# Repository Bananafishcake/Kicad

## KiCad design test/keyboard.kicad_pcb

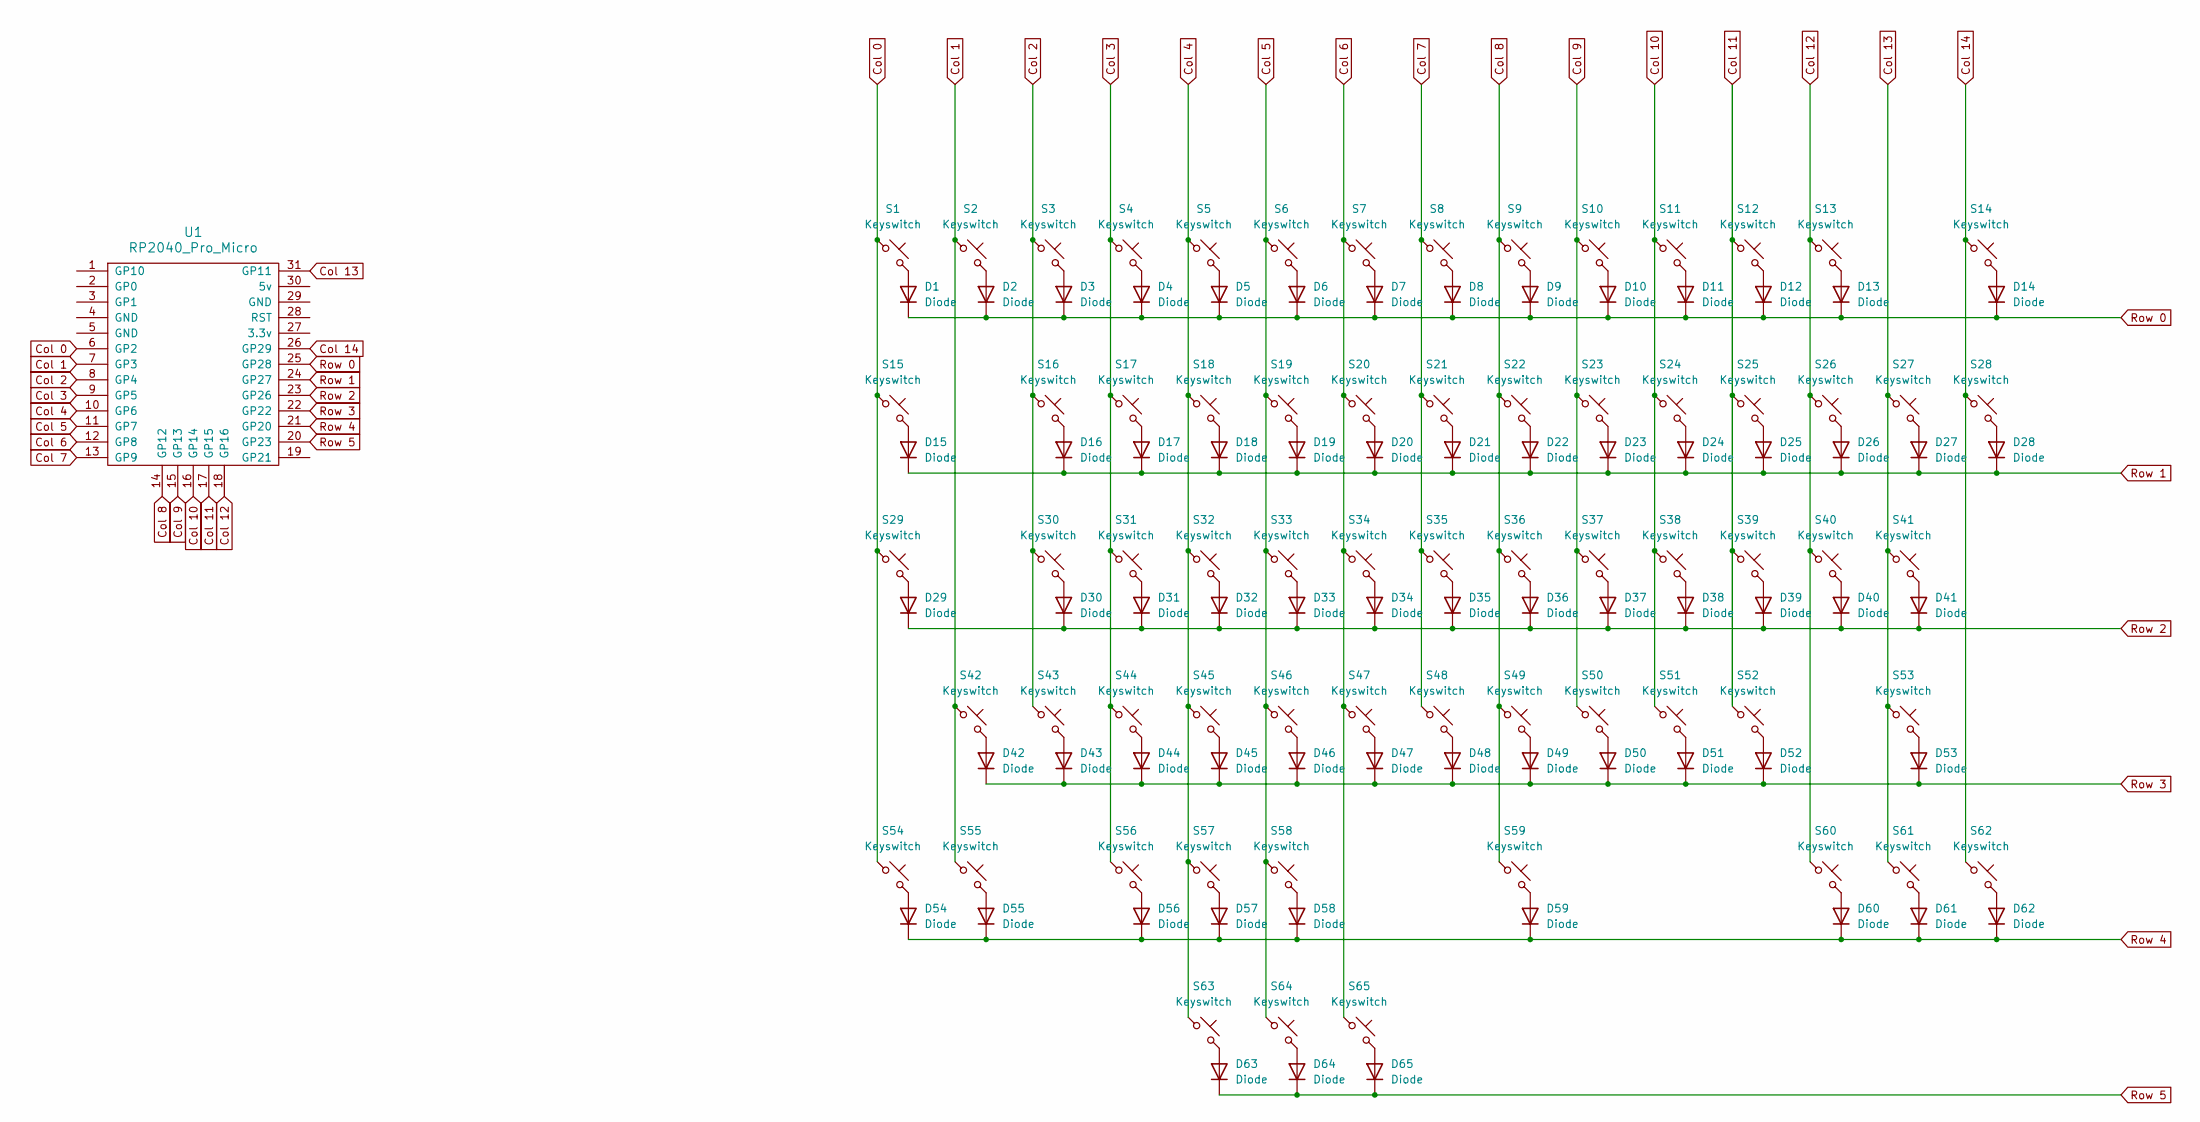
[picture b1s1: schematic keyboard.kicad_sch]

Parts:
D1, D2, D3, D4, D5, D6, D7, D8, D9, D10, D11, D12, D13, D14, D15, D16, D17, D18, D19, D20, D21, D22, D23, D24, D25, D26, D27, D28, D29, D30, D31, D32, D33, D34, D35, D36, D37, D38, D39, D40, D41, D42, D43, D44, D45, D46, D47, D48, D49, D50, D51, D52, D53, D54, D55, D56, D57, D58, D59, D60, D61, D62, D63, D64, D65: Diode; Diode_DO-35
S1, S2, S3, S4, S5, S6, S7, S8, S9, S10, S11, S12, S13, S16, S17, S18, S19, S20, S21, S22, S23, S24, S25, S26, S27, S30, S31, S32, S33, S34, S35, S36, S37, S38, S39, S40, S43, S44, S45, S46, S47, S48, S49, S50, S51, S52, S57, S58, S60, S61, S62, S63, S64, S65: Keyswitch; MX_PCB_1.00u
S14: Keyswitch; MX_PCB_2.00u
S15, S28: Keyswitch; MX_PCB_1.50u
S29: Keyswitch; MX_PCB_1.75u
S41, S42: Keyswitch; MX_PCB_2.25u
S53: Keyswitch; MX_PCB_2.75u
S54, S55, S56: Keyswitch; MX_PCB_1.25u
S59: Keyswitch; MX_PCB_6.25u
U1: RP2040_Pro_Micro

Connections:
Col 0: S1.1, S15.1, S29.1, S54.1, U1.6 (GP2)
Col 1: S2.1, S42.1, S55.1, U1.7 (GP3)
Col 2: S3.1, S16.1, S30.1, S43.1, U1.8 (GP4)
Col 3: S4.1, S17.1, S31.1, S44.1, S56.1, U1.9 (GP5)
Col 4: S5.1, S18.1, S32.1, S45.1, S57.1, S63.1, U1.10 (GP6)
Col 5: S6.1, S19.1, S33.1, S46.1, S58.1, S64.1, U1.11 (GP7)
Col 6: S7.1, S20.1, S34.1, S47.1, S65.1, U1.12 (GP8)
Col 7: S8.1, S21.1, S35.1, S48.1, U1.13 (GP9)
Col 8: S9.1, S22.1, S36.1, S49.1, S59.1, U1.14 (GP12)
Col 9: S10.1, S23.1, S37.1, S50.1, U1.15 (GP13)
Col 10: S11.1, S24.1, S38.1, S51.1, U1.16 (GP14)
Col 11: S12.1, S25.1, S39.1, S52.1, U1.17 (GP15)
Col 12: S13.1, S26.1, S40.1, S60.1, U1.18 (GP16)
Col 13: S27.1, S41.1, S53.1, S61.1, U1.31 (GP11)
Col 14: S14.1, S28.1, S62.1, U1.26 (GP29)
unnamed: D1.2 (A), S1.2
unnamed: D2.2 (A), S2.2
unnamed: D3.2 (A), S3.2
unnamed: D4.2 (A), S4.2
unnamed: D5.2 (A), S5.2
unnamed: D6.2 (A), S6.2
unnamed: D7.2 (A), S7.2
unnamed: D8.2 (A), S8.2
unnamed: D9.2 (A), S9.2
unnamed: D10.2 (A), S10.2
unnamed: D11.2 (A), S11.2
unnamed: D12.2 (A), S12.2
unnamed: D13.2 (A), S13.2
unnamed: D14.2 (A), S14.2
unnamed: D15.2 (A), S15.2
unnamed: D16.2 (A), S16.2
unnamed: D17.2 (A), S17.2
unnamed: D18.2 (A), S18.2
unnamed: D19.2 (A), S19.2
unnamed: D20.2 (A), S20.2
unnamed: D21.2 (A), S21.2
unnamed: D22.2 (A), S22.2
unnamed: D23.2 (A), S23.2
unnamed: D24.2 (A), S24.2
unnamed: D25.2 (A), S25.2
unnamed: D26.2 (A), S26.2
unnamed: D27.2 (A), S27.2
unnamed: D28.2 (A), S28.2
unnamed: D29.2 (A), S29.2
unnamed: D30.2 (A), S30.2
unnamed: D31.2 (A), S31.2
unnamed: D32.2 (A), S32.2
unnamed: D33.2 (A), S33.2
unnamed: D34.2 (A), S34.2
unnamed: D35.2 (A), S35.2
unnamed: D36.2 (A), S36.2
unnamed: D37.2 (A), S37.2
unnamed: D38.2 (A), S38.2
unnamed: D39.2 (A), S39.2
unnamed: D40.2 (A), S40.2
unnamed: D41.2 (A), S41.2
unnamed: D42.2 (A), S42.2
unnamed: D43.2 (A), S43.2
unnamed: D44.2 (A), S44.2
unnamed: D45.2 (A), S45.2
unnamed: D46.2 (A), S46.2
unnamed: D47.2 (A), S47.2
unnamed: D48.2 (A), S48.2
unnamed: D49.2 (A), S49.2
unnamed: D50.2 (A), S50.2
unnamed: D51.2 (A), S51.2
unnamed: D52.2 (A), S52.2
unnamed: D53.2 (A), S53.2
unnamed: D54.2 (A), S54.2
unnamed: D55.2 (A), S55.2
unnamed: D56.2 (A), S56.2
unnamed: D57.2 (A), S57.2
unnamed: D58.2 (A), S58.2
unnamed: D59.2 (A), S59.2
unnamed: D60.2 (A), S60.2
unnamed: D61.2 (A), S61.2
unnamed: D62.2 (A), S62.2
unnamed: D63.2 (A), S63.2
unnamed: D64.2 (A), S64.2
unnamed: D65.2 (A), S65.2
Row 0: D1.1 (K), D2.1 (K), D3.1 (K), D4.1 (K), D5.1 (K), D6.1 (K), D7.1 (K), D8.1 (K), D9.1 (K), D10.1 (K), D11.1 (K), D12.1 (K), D13.1 (K), D14.1 (K), U1.25 (GP28)
Row 1: D15.1 (K), D16.1 (K), D17.1 (K), D18.1 (K), D19.1 (K), D20.1 (K), D21.1 (K), D22.1 (K), D23.1 (K), D24.1 (K), D25.1 (K), D26.1 (K), D27.1 (K), D28.1 (K), U1.24 (GP27)
Row 2: D29.1 (K), D30.1 (K), D31.1 (K), D32.1 (K), D33.1 (K), D34.1 (K), D35.1 (K), D36.1 (K), D37.1 (K), D38.1 (K), D39.1 (K), D40.1 (K), D41.1 (K), U1.23 (GP26)
Row 3: D42.1 (K), D43.1 (K), D44.1 (K), D45.1 (K), D46.1 (K), D47.1 (K), D48.1 (K), D49.1 (K), D50.1 (K), D51.1 (K), D52.1 (K), D53.1 (K), U1.22 (GP22)
Row 4: D54.1 (K), D55.1 (K), D56.1 (K), D57.1 (K), D58.1 (K), D59.1 (K), D60.1 (K), D61.1 (K), D62.1 (K), U1.21 (GP20)
Row 5: D63.1 (K), D64.1 (K), D65.1 (K), U1.20 (GP23)

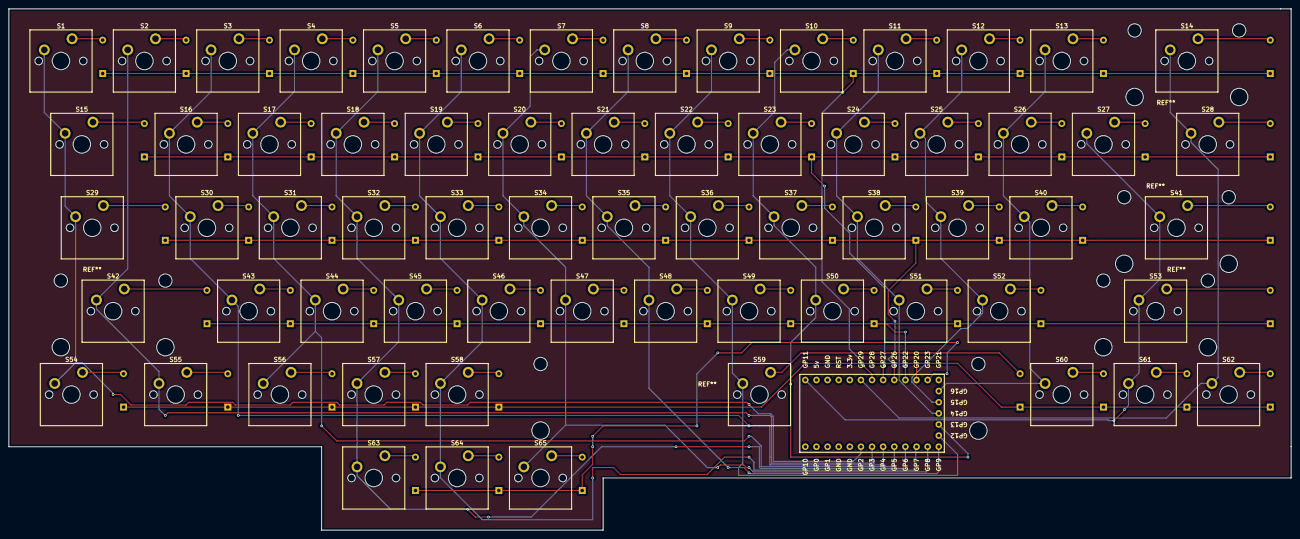
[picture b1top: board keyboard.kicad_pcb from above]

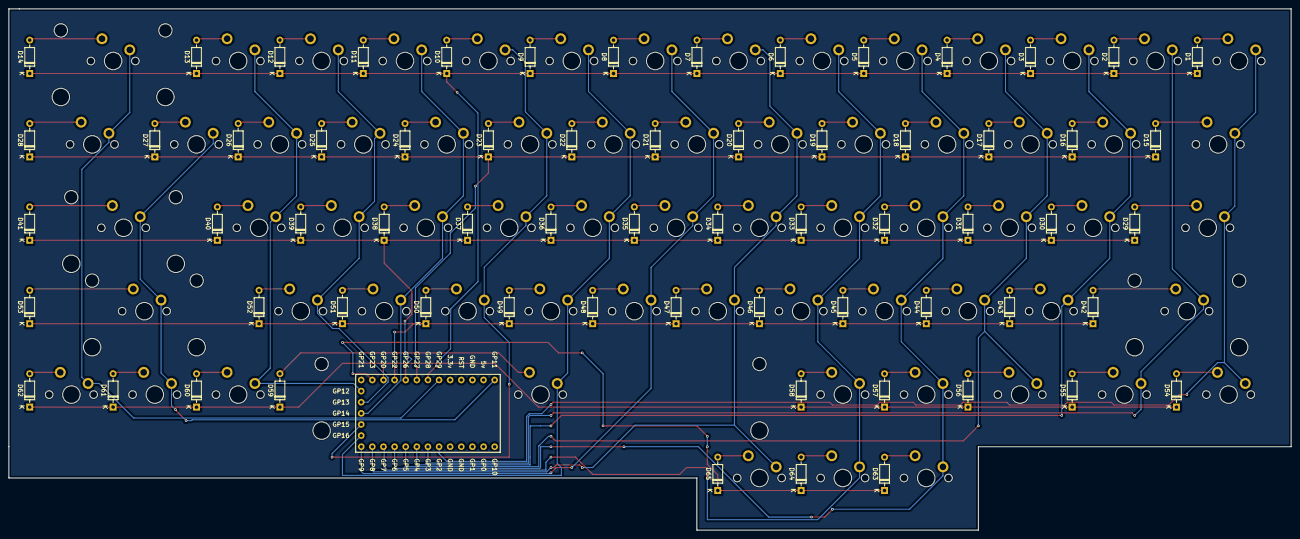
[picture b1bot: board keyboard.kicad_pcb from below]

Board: 2 copper layers, 292.9 x 119.1 mm, 131 parts (65 on the bottom side), 86 nets.

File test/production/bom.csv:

Designator,Footprint,Quantity,Value,LCSC Part #
"D1, D10, D11, D12, D13, D14, D15, D16, D17, D18, D19, D2, D20, D21, D22, D23, D24, D25, D26, D27, D28, D29, D3, D30, D31, D32, D33, D34, D35, D36, D37, D38, D39, D4, D40, D41, D42, D43, D44, D45, D46, D47, D48, D49, D5, D50, D51, D52, D53, D54, D55, D56, D57, D58, D59, D6, D60, D61, D62, D63, D64, D65, D7, D8, D9",Diode_DO-35,65,Diode,
"S1, S10, S11, S12, S13, S16, S17, S18, S19, S2, S20, S21, S22, S23, S24, S25, S26, S27, S3, S30, S31, S32, S33, S34, S35, S36, S37, S38, S39, S4, S40, S43, S44, S45, S46, S47, S48, S49, S5, S50, S51, S52, S57, S58, S6, S60, S61, S62, S63, S64, S65, S7, S8, S9",MX_PCB_1.00u,54,Keyswitch,
S14,MX_PCB_2.00u,1,Keyswitch,
"S15, S28",MX_PCB_1.50u,2,Keyswitch,
S29,MX_PCB_1.75u,1,Keyswitch,
"S41, S42",MX_PCB_2.25u,2,Keyswitch,
S53,MX_PCB_2.75u,1,Keyswitch,
"S54, S55, S56",MX_PCB_1.25u,3,Keyswitch,
S59,MX_PCB_6.25u,1,Keyswitch,
U1,RP2040_Pro_Micro,1,RP2040_Pro_Micro,
